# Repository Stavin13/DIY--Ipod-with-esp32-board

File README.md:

# ESP32-S3 iPod Music Player

A custom-built portable music player with modern touch interface and physical controls.

## Hardware Specifications

- **MCU**: ESP32-S3 (16MB Flash, 8MB PSRAM)
- **Display**: 2.8" ILI9341 capacitive touch (240x320px)
- **Storage**: 256GB microSD card
- **Audio**: USB-C (PCM2912A codec) + 3.5mm jack
- **Power**: USB-C PD (IP2723T) + 18650 LiPo (3500mAh)
- **Input**: Rotary encoder (KY-040) + capacitive touch
- **Connectivity**: Bluetooth 5.0 A2DP

## Key Features

- USB-C Power Delivery (15W charging)
- Simultaneous charging and digital audio output
- Bluetooth wireless streaming
- Touch + rotary encoder navigation
- 24-bit/96kHz audio quality
- 6-8 hours battery life
- OTA updates

## Development Phases

1. **Phase 1**: Core Hardware Setup
2. **Phase 2**: Basic Software (Display, SD, Audio, Encoder)
3. **Phase 3**: Advanced Features (USB-C, Bluetooth, Touch)
4. **Phase 4**: Polish (Album Art, Animations, EQ)

## Budget: ₹3,450 (~$45 USD)

## Timeline: 12 weeks

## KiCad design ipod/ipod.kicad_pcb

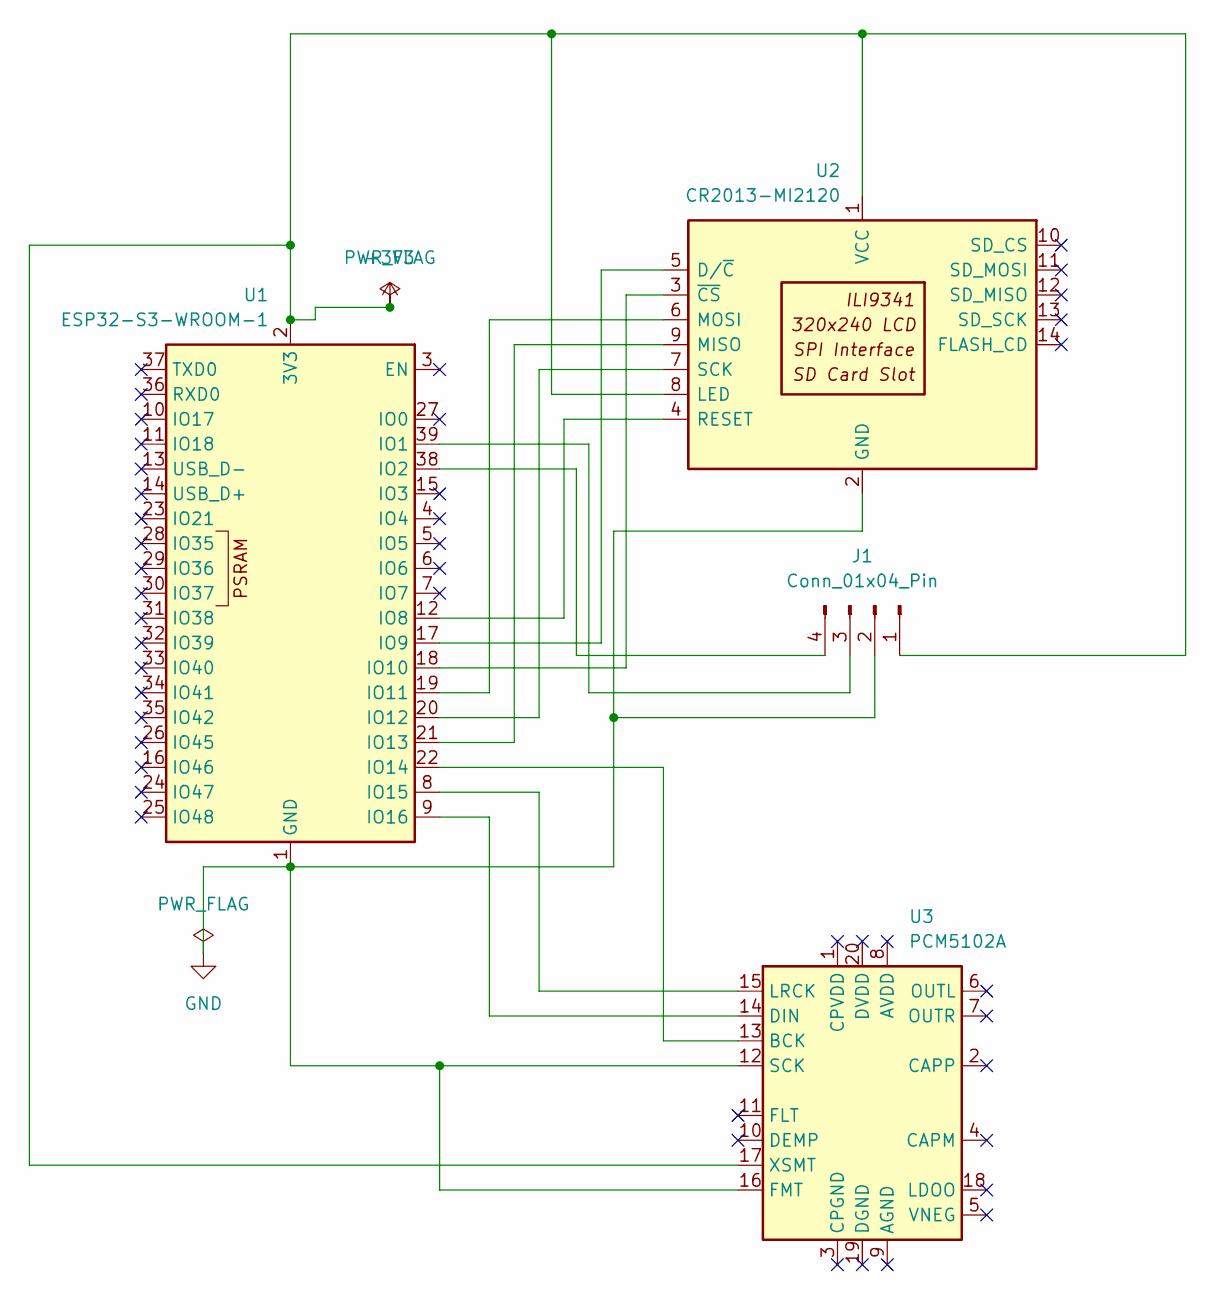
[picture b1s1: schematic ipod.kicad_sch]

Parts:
J1: Conn_01x04_Pin; FanPinHeader_1x04_P2.54mm_Vertical
U1: ESP32-S3-WROOM-1
U2: CR2013-MI2120
U3: PCM5102A; TSSOP-20_4.4x6.5mm_P0.65mm

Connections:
+3V3: J1.1, U1.2 (3V3), U2.1 (VCC), U2.8 (LED), U3.17 (XSMT)
GND: J1.2, U1.1 (GND), U1.40 (GND), U1.41 (GND), U2.2 (GND), U3.12 (SCK), U3.16 (FMT)
unnamed: J1.3, U1.39 (IO1)
unnamed: J1.4, U1.38 (IO2)
unnamed: U1.12 (IO8), U2.4 (RESET)
unnamed: U1.17 (IO9), U2.5 (D/~C)
unnamed: U1.18 (IO10), U2.3 (~CS)
unnamed: U1.19 (IO11), U2.6 (MOSI)
unnamed: U1.20 (IO12), U2.7 (SCK)
unnamed: U1.21 (IO13), U2.9 (MISO)
unnamed: U1.22 (IO14), U3.13 (BCK)
unnamed: U1.8 (IO15), U3.15 (LRCK)
unnamed: U1.9 (IO16), U3.14 (DIN)

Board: 2 copper layers, 4 parts (0 on the bottom side), 13 nets, no tracks yet.
